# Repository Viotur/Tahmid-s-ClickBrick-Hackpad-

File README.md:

# Tahmid-s-ClickBrick-Hackpad-
Hi! I'm Tahmid, and this is my Hackpad submission for the Blueprint program. I took inspiration from Imran's project, which can be found here: https://github.com/Voltyggs/Imran-s-lil-macropad/

For this project, I designed a custom macropad using the Seeed XIAO RP2040 DIP as the microcontroller. The macropad features eight Cherry MX switches with keycaps and an EC11 Rotary Encoder switch.

Below is an overview image showing the completed macropad design:

I tried to keep everything simple and minimal, and I think it turned out pretty well.

Here’s a look at the schematic:

Next, here’s the PCB:

Now, let’s check out the case:

Here’s what you’ll need for the project:

1x SEEED XIAO RP2040-DIP,
1x EC11 Rotary Encoder switch,
4x M3x16mm screws,
8x Cherry MX switches,
8x keycaps for the Cherry MX switches

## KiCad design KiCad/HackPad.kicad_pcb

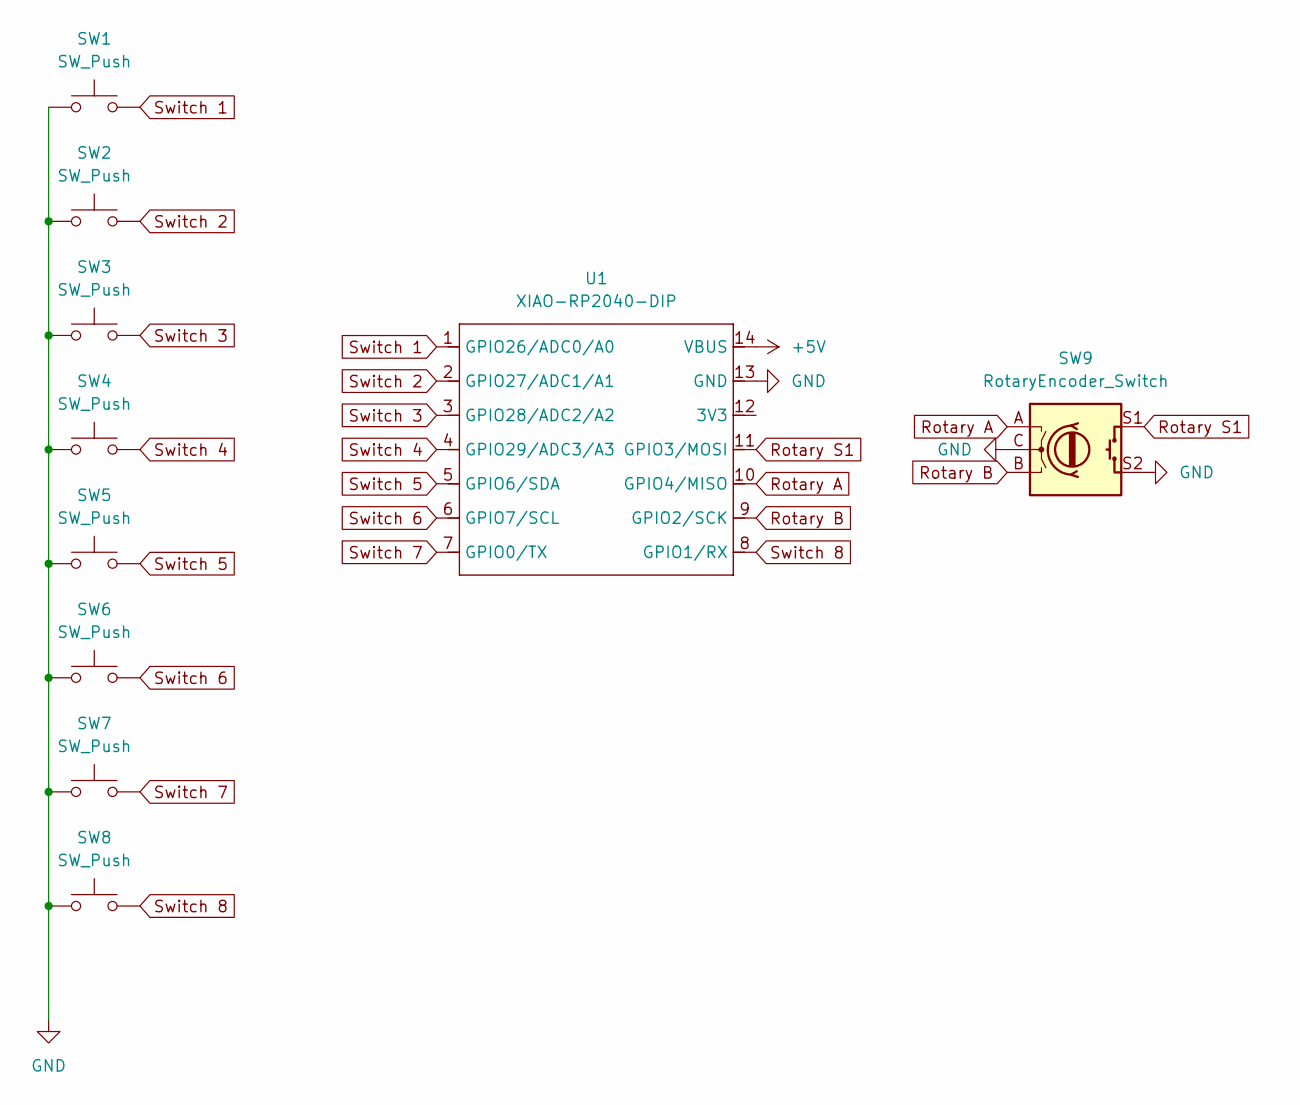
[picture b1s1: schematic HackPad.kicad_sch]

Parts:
SW1, SW2, SW3, SW4, SW5, SW6, SW7, SW8: SW_Push; MX_PCB_1.00u
SW9: RotaryEncoder_Switch; RotaryEncoder_Alps_EC11E-Switch_Vertical_H20mm
U1: XIAO-RP2040-DIP

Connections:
+5V: U1.14 (VBUS)
GND: SW1.1, SW2.1, SW3.1, SW4.1, SW5.1, SW6.1, SW7.1, SW8.1, SW9.C, SW9.S2, U1.13 (GND)
Rotary A: SW9.A, U1.10 (GPIO4/MISO)
Rotary B: SW9.B, U1.9 (GPIO2/SCK)
Rotary S1: SW9.S1, U1.11 (GPIO3/MOSI)
Switch 1: SW1.2, U1.1 (GPIO26/ADC0/A0)
Switch 2: SW2.2, U1.2 (GPIO27/ADC1/A1)
Switch 3: SW3.2, U1.3 (GPIO28/ADC2/A2)
Switch 4: SW4.2, U1.4 (GPIO29/ADC3/A3)
Switch 5: SW5.2, U1.5 (GPIO6/SDA)
Switch 6: SW6.2, U1.6 (GPIO7/SCL)
Switch 7: SW7.2, U1.7 (GPIO0/TX)
Switch 8: SW8.2, U1.8 (GPIO1/RX)

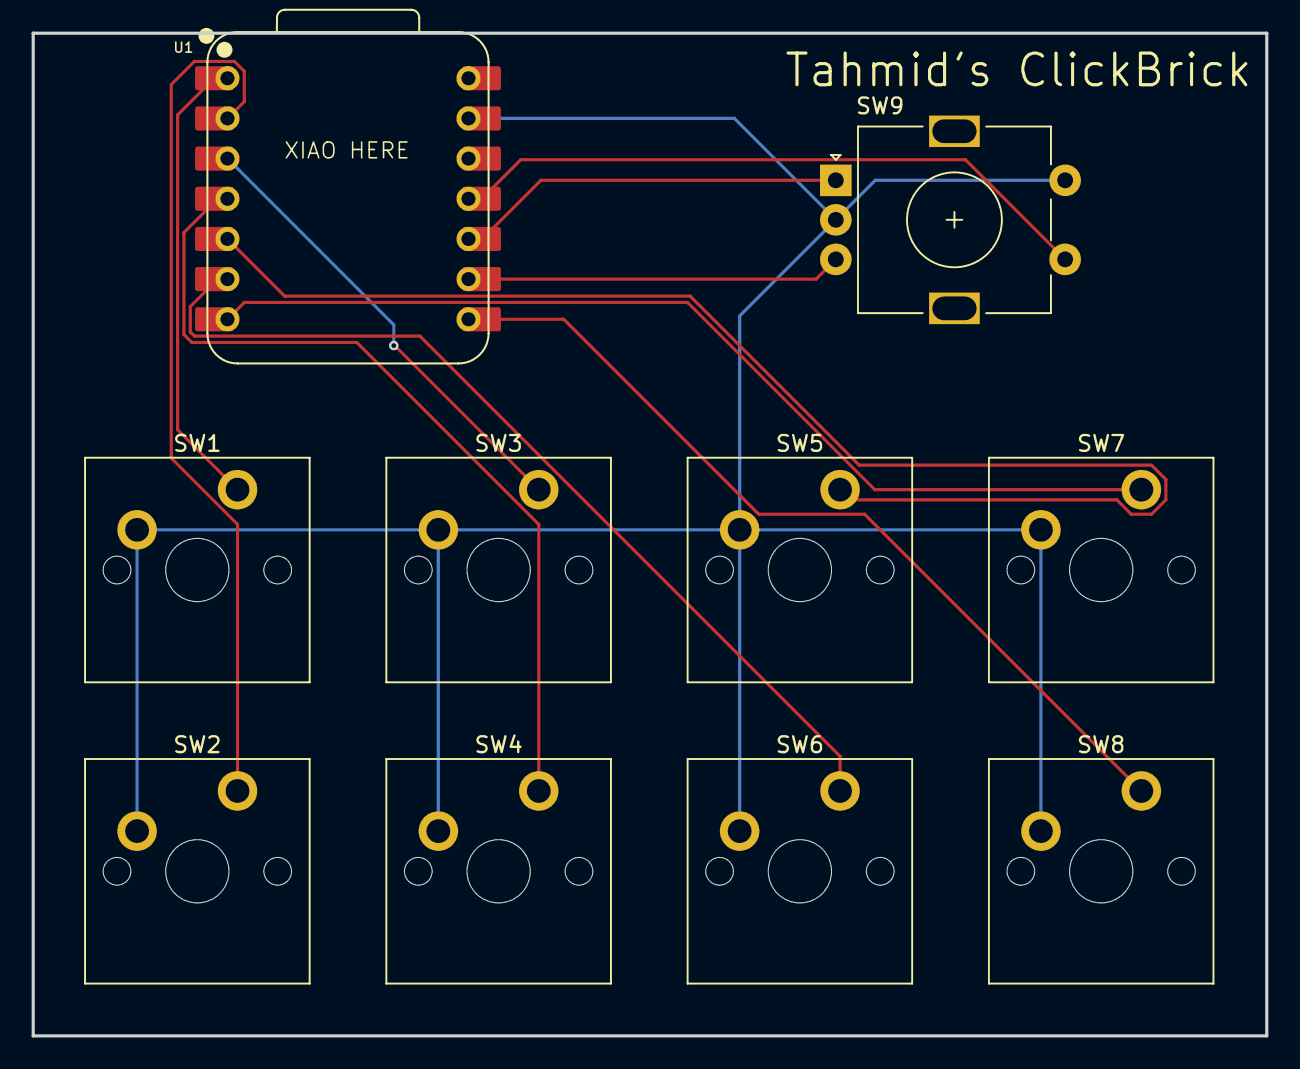
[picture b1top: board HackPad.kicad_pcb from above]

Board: 2 copper layers, 78.0 x 63.4 mm, 10 parts (0 on the bottom side), 12 nets.
